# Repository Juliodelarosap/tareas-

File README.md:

# tareas-
tareas de programacion mecatronicos 
c3-2022
Nombre: Julio de la Rosa 
Matricula: 2018-6732

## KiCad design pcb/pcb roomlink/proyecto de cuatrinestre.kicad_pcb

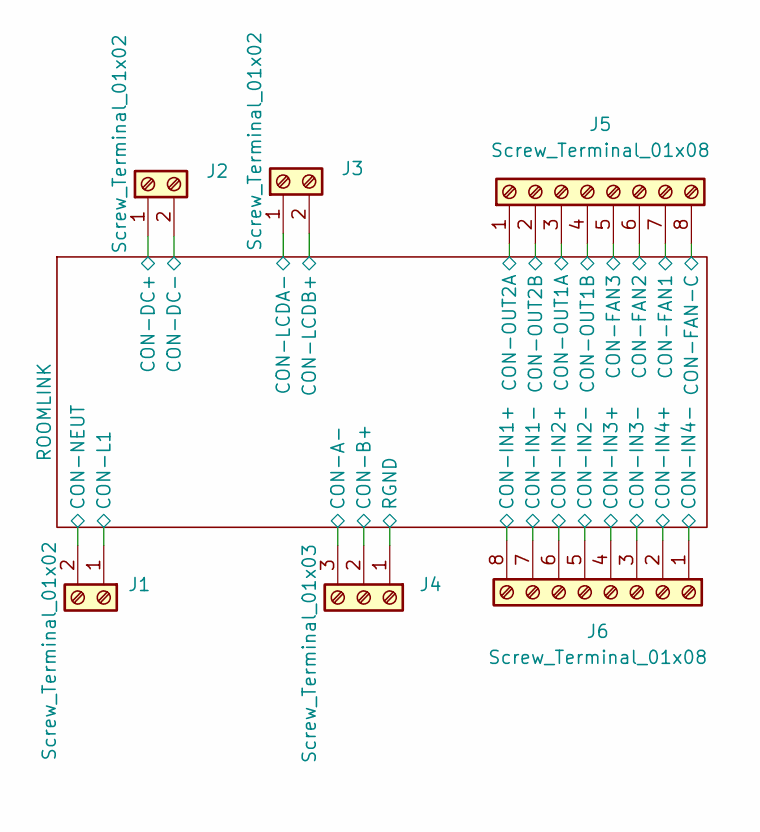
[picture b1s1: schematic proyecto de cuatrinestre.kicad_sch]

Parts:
J1, J2, J3: Screw_Terminal_01x02; CUI_TBP04R12-500-02GR
J4: Screw_Terminal_01x03; CUI_TBP04R12-500-03GR
J5, J6: Screw_Terminal_01x08; CUI_TBP04R12-500-08GR

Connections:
/ROOMLINK/CON-A-: J4.3; also elsewhere on the board
/ROOMLINK/CON-B+: J4.2; also elsewhere on the board
/ROOMLINK/CON-DC+: J2.1; also elsewhere on the board
/ROOMLINK/CON-DC-: J2.2; also elsewhere on the board
/ROOMLINK/CON-FAN1: J5.7; also elsewhere on the board
/ROOMLINK/CON-FAN2: J5.6; also elsewhere on the board
/ROOMLINK/CON-FAN3: J5.5; also elsewhere on the board
/ROOMLINK/CON-FAN-C: J5.8; also elsewhere on the board
/ROOMLINK/CON-IN1+: J6.8; also elsewhere on the board
/ROOMLINK/CON-IN1-: J6.7; also elsewhere on the board
/ROOMLINK/CON-IN2+: J6.6; also elsewhere on the board
/ROOMLINK/CON-IN2-: J6.5; also elsewhere on the board
/ROOMLINK/CON-IN3+: J6.4; also elsewhere on the board
/ROOMLINK/CON-IN3-: J6.3; also elsewhere on the board
/ROOMLINK/CON-IN4+: J6.2; also elsewhere on the board
/ROOMLINK/CON-IN4-: J6.1; also elsewhere on the board
/ROOMLINK/CON-L1: J1.1; also elsewhere on the board
/ROOMLINK/CON-LCDA-: J3.1; also elsewhere on the board
/ROOMLINK/CON-LCDB+: J3.2; also elsewhere on the board
/ROOMLINK/CON-NEUT: J1.2; also elsewhere on the board
/ROOMLINK/CON-OUT1A: J5.3; also elsewhere on the board
/ROOMLINK/CON-OUT1B: J5.4; also elsewhere on the board
/ROOMLINK/CON-OUT2A: J5.1; also elsewhere on the board
/ROOMLINK/CON-OUT2B: J5.2; also elsewhere on the board
/ROOMLINK/RGND: J4.1; also elsewhere on the board

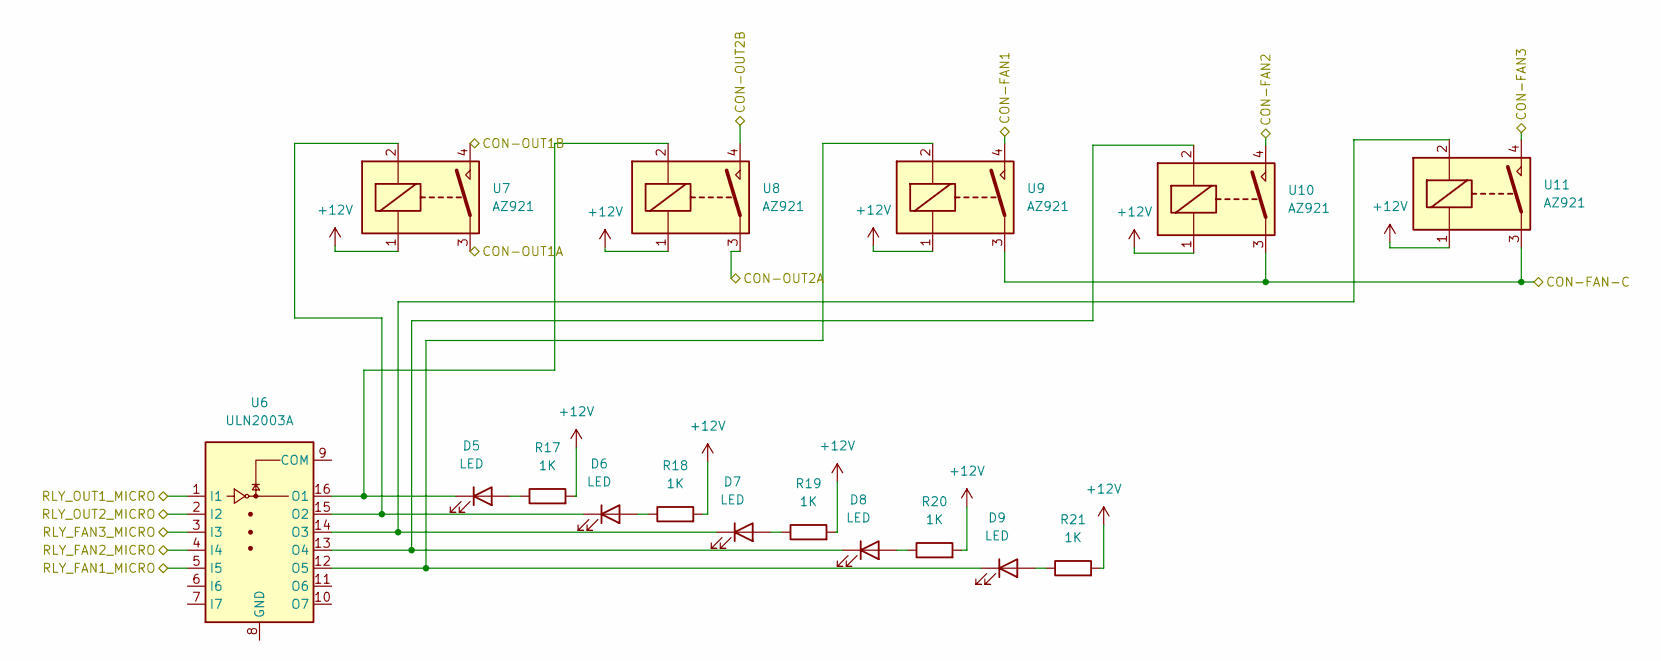
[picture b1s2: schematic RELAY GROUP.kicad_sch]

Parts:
D5, D6, D7, D8, D9: LED; LED_0805_2012Metric
R17, R18, R19, R20, R21: 1K; R_0805_2012Metric
U6: ULN2003A; SOIC-16_3.9x9.9mm_P1.27mm
U7, U8, U9, U10, U11: AZ921

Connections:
+12V: R17.2, R18.2, R19.2, R20.2, R21.2, U7.1, U8.1, U9.1, U10.1, U11.1; also elsewhere on the board
/ROOMLINK/CON-FAN1: U9.4; also elsewhere on the board
/ROOMLINK/CON-FAN2: U10.4; also elsewhere on the board
/ROOMLINK/CON-FAN3: U11.4; also elsewhere on the board
/ROOMLINK/CON-FAN-C: U9.3, U10.3, U11.3; also elsewhere on the board
/ROOMLINK/CON-OUT1A: U7.3; also elsewhere on the board
/ROOMLINK/CON-OUT1B: U7.4; also elsewhere on the board
/ROOMLINK/CON-OUT2A: U8.3; also elsewhere on the board
/ROOMLINK/CON-OUT2B: U8.4; also elsewhere on the board
/ROOMLINK/CONTROL/RLY_FAN1_MICRO: U6.5 (I5); also elsewhere on the board
/ROOMLINK/CONTROL/RLY_FAN2_MICRO: U6.4 (I4); also elsewhere on the board
/ROOMLINK/CONTROL/RLY_FAN3_MICRO: U6.3 (I3); also elsewhere on the board
/ROOMLINK/CONTROL/RLY_OUT1_MICRO: U6.1 (I1); also elsewhere on the board
/ROOMLINK/CONTROL/RLY_OUT2_MICRO: U6.2 (I2); also elsewhere on the board
unnamed: D5.2 (A), R17.1
unnamed: D5.1 (K), U6.16 (O1), U8.2
unnamed: D6.2 (A), R18.1
unnamed: D6.1 (K), U6.15 (O2), U7.2
unnamed: D7.2 (A), R19.1
unnamed: D7.1 (K), U6.14 (O3), U11.2
unnamed: D8.2 (A), R20.1
unnamed: D8.1 (K), U6.13 (O4), U10.2
unnamed: D9.2 (A), R21.1
unnamed: D9.1 (K), U6.12 (O5), U9.2

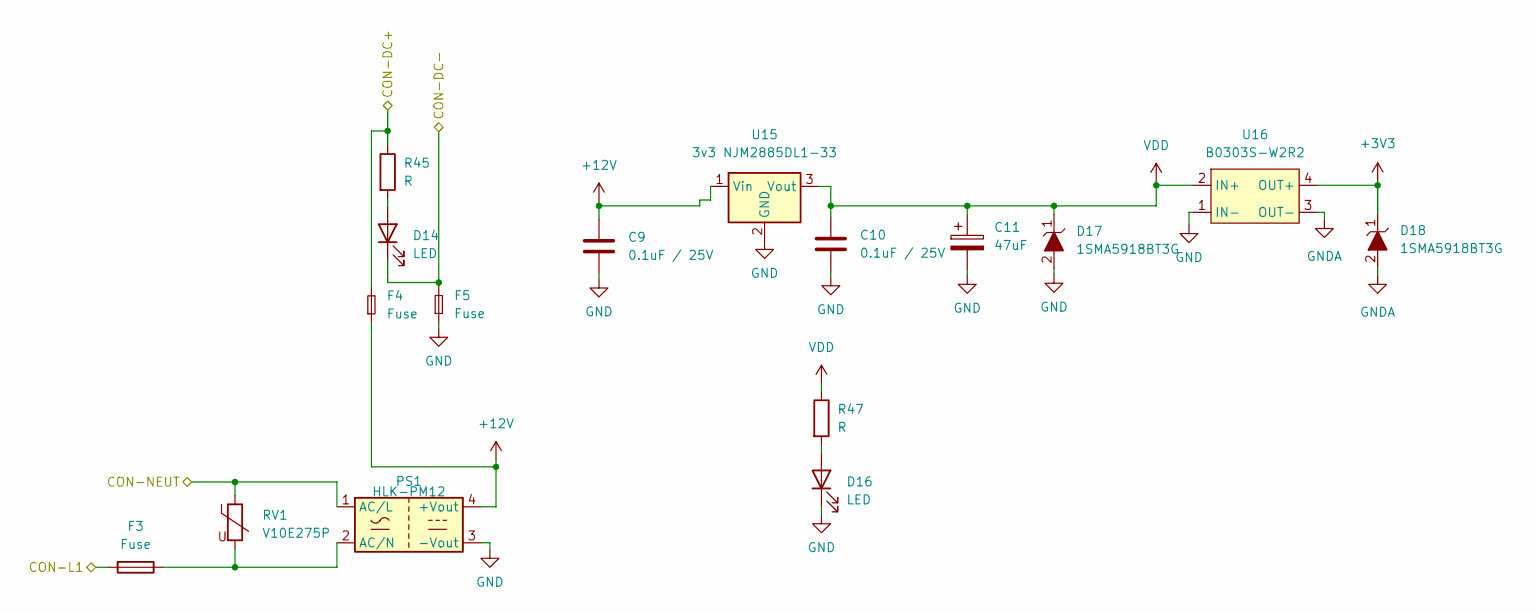
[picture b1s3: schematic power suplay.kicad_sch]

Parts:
C9, C10: 0.1uF / 25V; C_0805_2012Metric
C11: 47uF; CP_Elec_6.3x5.7
D14, D16: LED; LED_0805_2012Metric
D17, D18: 1SMA5918BT3G; D_SMB
F3: Fuse; Fuseholder_Cylinder-5x20mm_Schurter_0031_8201_Horizontal_Op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
F4, F5: Fuse; RESC3115X65N
PS1: HLK-PM12; Converter_ACDC_HiLink_HLK-PMxx
R45, R47: R; R_0805_2012Metric
RV1: V10E275P; VAR_B72210S1140K501
U15: 3v3 NJM2885DL1-33; TO-252-2
U16: B0303S-W2R2; CONV_B0505S-1WR2

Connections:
+3V3: D18.1, U16.4 (OUT+); also elsewhere on the board
+12V: C9.1, F4.1, PS1.4 (+Vout), U15.1 (Vin); also elsewhere on the board
/ROOMLINK/CON-DC+: F4.2, R45.1; also elsewhere on the board
/ROOMLINK/CON-DC-: D14.1 (K), F5.2; also elsewhere on the board
/ROOMLINK/CON-L1: F3.2; also elsewhere on the board
/ROOMLINK/CON-NEUT: PS1.1 (AC/L), RV1.1; also elsewhere on the board
GND: C9.2, C10.2, C11.2, D16.1 (K), D17.2, F5.1, PS1.3 (-Vout), U15.2 (GND), U16.1 (IN-); also elsewhere on the board
GNDA: D18.2, U16.3 (OUT-); also elsewhere on the board
unnamed: D14.2 (A), R45.2
unnamed: D16.2 (A), R47.2
unnamed: F3.1, PS1.2 (AC/N), RV1.2
VDD: C10.1, C11.1, D17.1, R47.1, U15.3 (Vout), U16.2 (IN+); also elsewhere on the board

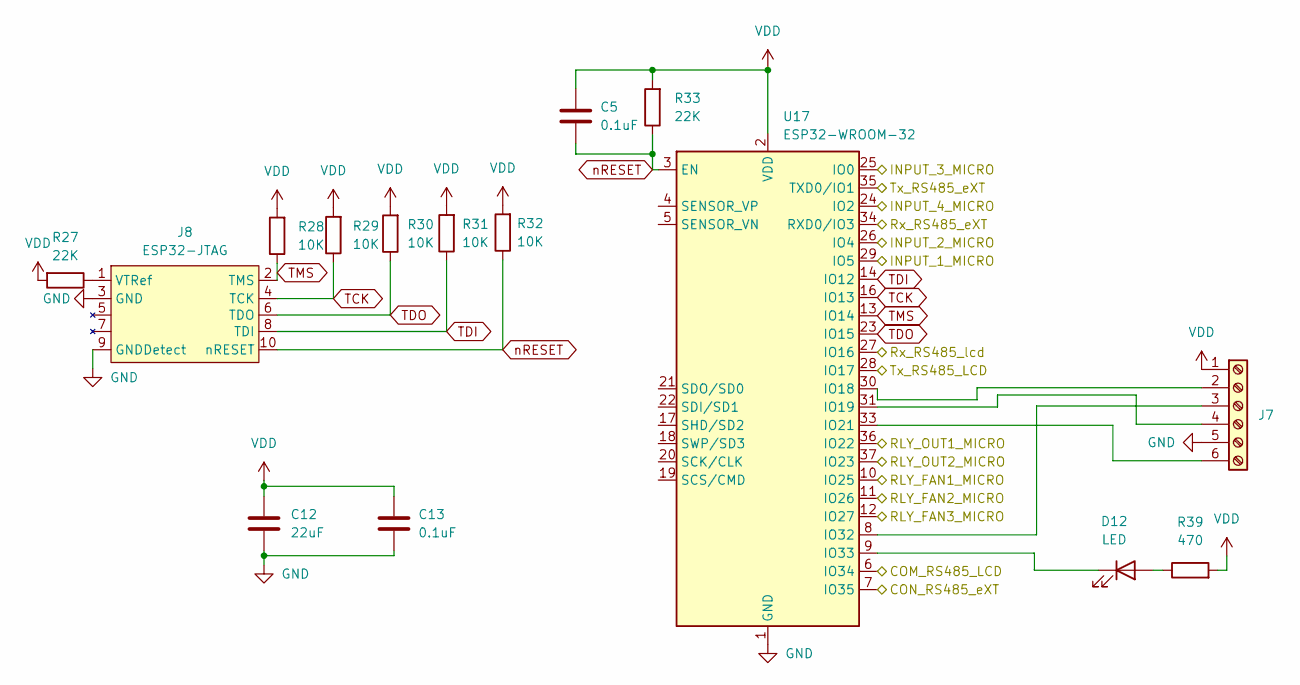
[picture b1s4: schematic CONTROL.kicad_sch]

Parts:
C5, C13: 0.1uF; C_0805_2012Metric
C12: 22uF; C_0805_2012Metric
D12: LED; LED_0805_2012Metric
J7: Screw_Terminal_01x06; PinHeader_2x03_P2.54mm_Vertical
J8: ESP32-JTAG; PinHeader_2x05_P2.54mm_Vertical
R27, R33: 22K; R_0805_2012Metric
R28, R29, R30, R31, R32: 10K; R_0805_2012Metric
R39: 470; R_0805_2012Metric
U17: ESP32-WROOM-32

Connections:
/ROOMLINK/CONTROL/COM_RS485_LCD: U17.6 (IO34); also elsewhere on the board
/ROOMLINK/CONTROL/CON_RS485_eXT: U17.7 (IO35); also elsewhere on the board
/ROOMLINK/CONTROL/INPUT_1_MICRO: U17.29 (IO5); also elsewhere on the board
/ROOMLINK/CONTROL/INPUT_2_MICRO: U17.26 (IO4); also elsewhere on the board
/ROOMLINK/CONTROL/INPUT_3_MICRO: U17.25 (IO0); also elsewhere on the board
/ROOMLINK/CONTROL/INPUT_4_MICRO: U17.24 (IO2); also elsewhere on the board
/ROOMLINK/CONTROL/RLY_FAN1_MICRO: U17.10 (IO25); also elsewhere on the board
/ROOMLINK/CONTROL/RLY_FAN2_MICRO: U17.11 (IO26); also elsewhere on the board
/ROOMLINK/CONTROL/RLY_FAN3_MICRO: U17.12 (IO27); also elsewhere on the board
/ROOMLINK/CONTROL/RLY_OUT1_MICRO: U17.36 (IO22); also elsewhere on the board
/ROOMLINK/CONTROL/RLY_OUT2_MICRO: U17.37 (IO23); also elsewhere on the board
/ROOMLINK/CONTROL/Rx_RS485_eXT: U17.34 (RXD0/IO3); also elsewhere on the board
/ROOMLINK/CONTROL/Rx_RS485_lcd: U17.27 (IO16); also elsewhere on the board
/ROOMLINK/CONTROL/Tx_RS485_LCD: U17.28 (IO17); also elsewhere on the board
/ROOMLINK/CONTROL/Tx_RS485_eXT: U17.35 (TXD0/IO1); also elsewhere on the board
GND: C12.2, C13.2, J7.5, J8.3 (GND), J8.9 (GNDDetect), U17.1 (GND), U17.15 (GND), U17.38 (GND), U17.39 (GND); also elsewhere on the board
unnamed: D12.2 (A), R39.1
unnamed: D12.1 (K), U17.9 (IO33)
unnamed: J7.2, U17.30 (IO18)
unnamed: J7.3, U17.8 (IO32)
unnamed: J7.4, U17.31 (IO19)
unnamed: J7.6, U17.33 (IO21)
unnamed: J8.1 (VTRef), R27.1
TCK: J8.4 (TCK), R29.1, U17.16 (IO13)
TDI: J8.8 (TDI), R31.1, U17.14 (IO12)
TDO: J8.6 (TDO), R30.1, U17.23 (IO15)
TMS: J8.2 (TMS), R28.1, U17.13 (IO14)
VDD: C5.1, C12.1, C13.1, J7.1, R27.2, R28.2, R29.2, R30.2, R31.2, R32.2, R33.2, R39.2, U17.2 (VDD); also elsewhere on the board
nRESET: C5.2, J8.10 (nRESET), R32.1, R33.1, U17.3 (EN)

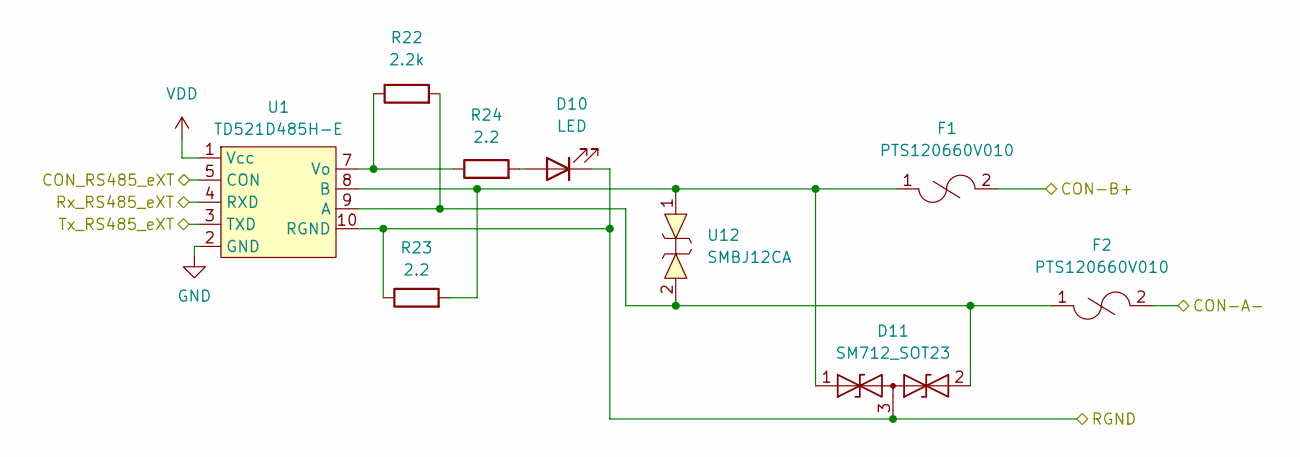
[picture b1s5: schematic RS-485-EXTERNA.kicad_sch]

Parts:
D10: LED; LED_0805_2012Metric
D11: SM712_SOT23; SOT-23
F1, F2: PTS120660V010; RESC3115X65N
R22: 2.2k; R_0805_2012Metric
R23, R24: 2.2; R_0805_2012Metric
U1: TD521D485H-E
U12: SMBJ12CA

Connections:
/ROOMLINK/CON-A-: F2.2; also elsewhere on the board
/ROOMLINK/CON-B+: F1.2; also elsewhere on the board
/ROOMLINK/CONTROL/CON_RS485_eXT: U1.5 (CON); also elsewhere on the board
/ROOMLINK/CONTROL/Rx_RS485_eXT: U1.4 (RXD); also elsewhere on the board
/ROOMLINK/CONTROL/Tx_RS485_eXT: U1.3 (TXD); also elsewhere on the board
/ROOMLINK/RGND: D10.1 (K), D11.3 (common), R23.1, U1.10 (RGND); also elsewhere on the board
GND: U1.2 (GND); also elsewhere on the board
unnamed: D10.2 (A), R24.2
unnamed: D11.1 (A1), F1.1, R23.2, U1.8 (B), U12.1
unnamed: D11.2 (A2), F2.1, R22.2, U1.9 (A), U12.2
unnamed: R22.1, R24.1, U1.7 (Vo)
VDD: U1.1 (Vcc); also elsewhere on the board

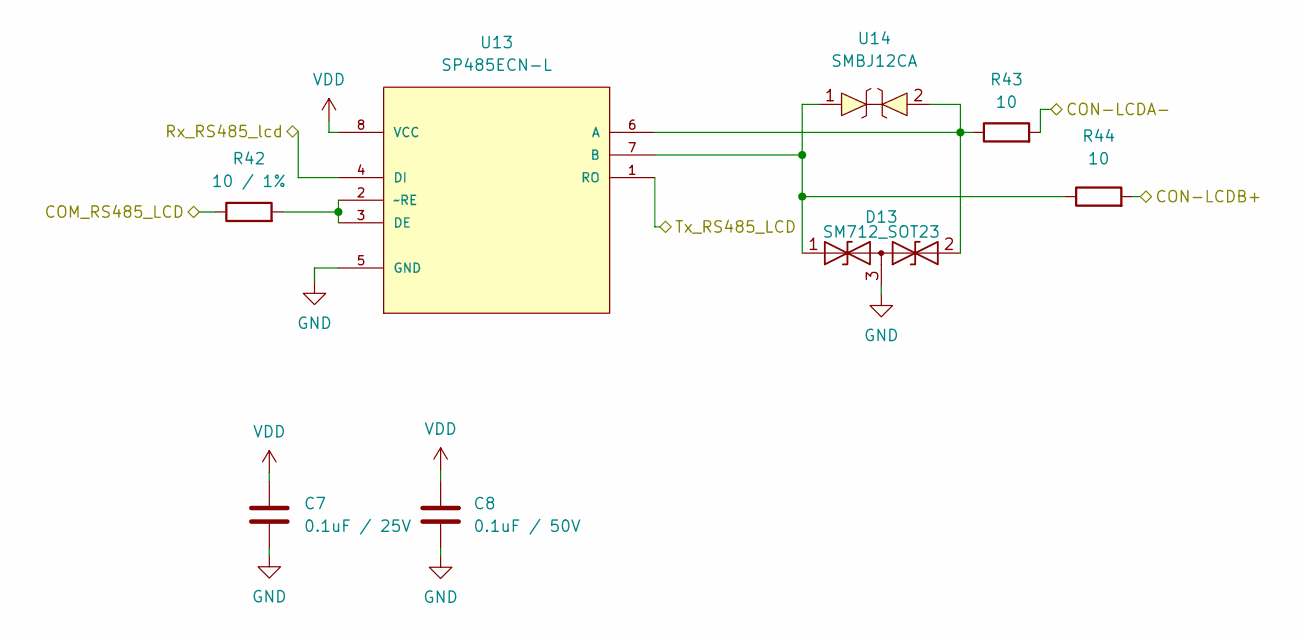
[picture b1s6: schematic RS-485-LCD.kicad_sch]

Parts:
C7: 0.1uF / 25V; C_0805_2012Metric
C8: 0.1uF / 50V; C_0805_2012Metric
D13: SM712_SOT23; SOT-23
R42: 10 / 1%; R_0805_2012Metric
R43, R44: 10; R_0805_2012Metric
U13: SP485ECN-L; SOIC127P600X175-8N; MPN SP485ECN-L
U14: SMBJ12CA

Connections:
/ROOMLINK/CON-LCDA-: R43.2; also elsewhere on the board
/ROOMLINK/CON-LCDB+: R44.2; also elsewhere on the board
/ROOMLINK/CONTROL/COM_RS485_LCD: R42.1; also elsewhere on the board
/ROOMLINK/CONTROL/Rx_RS485_lcd: U13.4 (DI); also elsewhere on the board
/ROOMLINK/CONTROL/Tx_RS485_LCD: U13.1 (RO); also elsewhere on the board
GND: C7.2, C8.2, D13.3 (common), U13.5 (GND); also elsewhere on the board
unnamed: D13.1 (A1), R44.1, U13.7 (B), U14.1
unnamed: D13.2 (A2), R43.1, U13.6 (A), U14.2
unnamed: R42.2, U13.2 (~RE), U13.3 (DE)
VDD: C7.1, C8.1, U13.8 (VCC); also elsewhere on the board

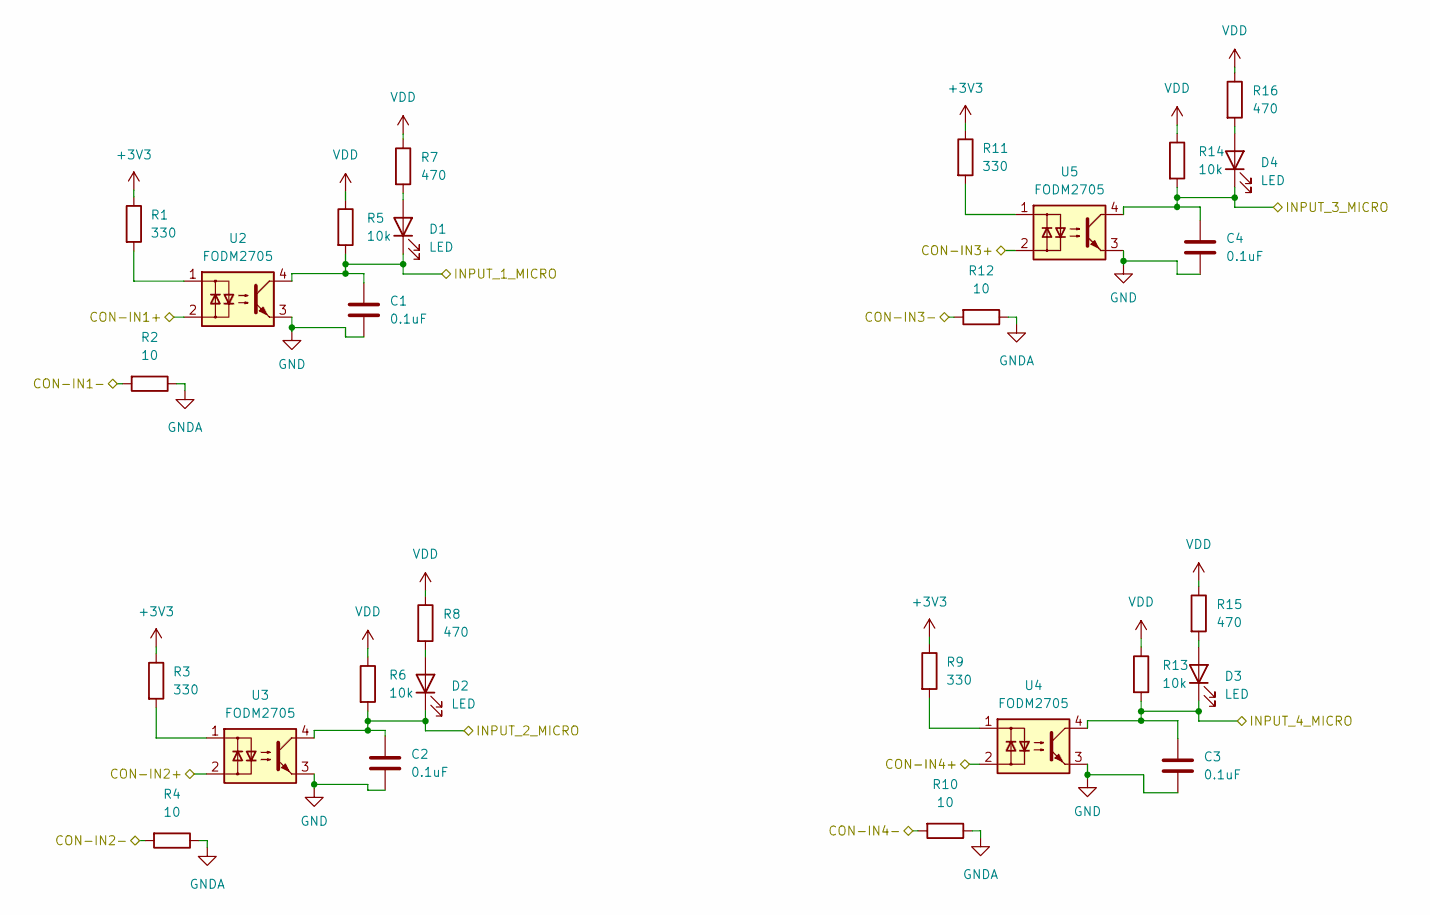
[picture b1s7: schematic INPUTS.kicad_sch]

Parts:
C1, C2, C3, C4: 0.1uF; C_0805_2012Metric
D1, D2, D3, D4: LED; LED_0805_2012Metric
R1, R3, R9, R11: 330; R_0805_2012Metric
R2, R4, R10, R12: 10; R_0805_2012Metric
R5, R6, R13, R14: 10k; R_0805_2012Metric
R7, R8, R15, R16: 470; R_0805_2012Metric
U2, U3, U4, U5: FODM2705

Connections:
+3V3: R1.1, R3.1, R9.1, R11.1; also elsewhere on the board
/ROOMLINK/CON-IN1+: U2.2; also elsewhere on the board
/ROOMLINK/CON-IN1-: R2.2; also elsewhere on the board
/ROOMLINK/CON-IN2+: U3.2; also elsewhere on the board
/ROOMLINK/CON-IN2-: R4.2; also elsewhere on the board
/ROOMLINK/CON-IN3+: U5.2; also elsewhere on the board
/ROOMLINK/CON-IN3-: R12.2; also elsewhere on the board
/ROOMLINK/CON-IN4+: U4.2; also elsewhere on the board
/ROOMLINK/CON-IN4-: R10.2; also elsewhere on the board
/ROOMLINK/CONTROL/INPUT_1_MICRO: C1.1, D1.1 (K), R5.2, U2.4; also elsewhere on the board
/ROOMLINK/CONTROL/INPUT_2_MICRO: C2.1, D2.1 (K), R6.2, U3.4; also elsewhere on the board
/ROOMLINK/CONTROL/INPUT_3_MICRO: C4.1, D4.1 (K), R14.2, U5.4; also elsewhere on the board
/ROOMLINK/CONTROL/INPUT_4_MICRO: C3.1, D3.1 (K), R13.2, U4.4; also elsewhere on the board
GND: C1.2, C2.2, C3.2, C4.2, U2.3, U3.3, U4.3, U5.3; also elsewhere on the board
GNDA: R2.1, R4.1, R10.1, R12.1; also elsewhere on the board
unnamed: D1.2 (A), R7.2
unnamed: D2.2 (A), R8.2
unnamed: D3.2 (A), R15.2
unnamed: D4.2 (A), R16.2
unnamed: R1.2, U2.1
unnamed: R3.2, U3.1
unnamed: R9.2, U4.1
unnamed: R11.2, U5.1
VDD: R5.1, R6.1, R7.1, R8.1, R13.1, R14.1, R15.1, R16.1; also elsewhere on the board

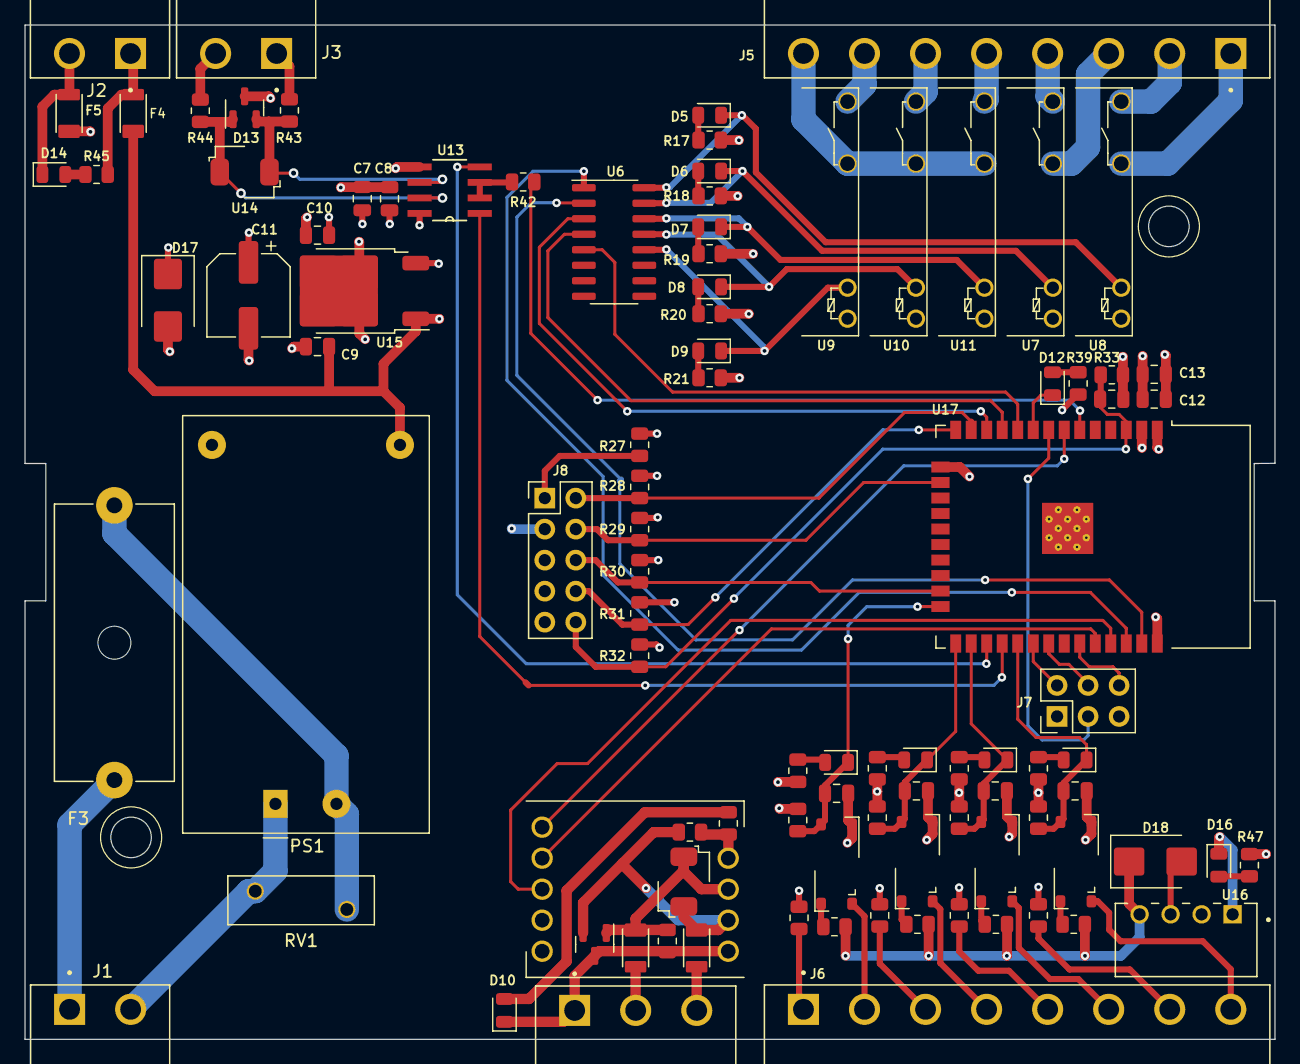
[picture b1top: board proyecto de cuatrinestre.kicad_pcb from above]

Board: 4 copper layers, 102.4 x 83.1 mm, 98 parts (0 on the bottom side), 85 nets.

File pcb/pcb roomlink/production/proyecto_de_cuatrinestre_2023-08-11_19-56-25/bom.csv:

Designator,Footprint,Quantity,Value,LCSC Part #
"C1, C13, C2, C3, C4, C5",0805,6,0.1uF,
"C10, C7, C9",0805,3,0.1uF / 25V,
C11,CP_Elec_6.3x5.7,1,47uF,
C12,0805,1,22uF,
C8,0805,1,0.1uF / 50V,
"D1, D10, D12, D14, D16, D2, D3, D4, D5, D6, D7, D8, D9",0805,13,LED,
"D11, D13",SOT-23,2,SM712_SOT23,
"D17, D18",D_SMB,2,1SMA5918BT3G,
"F1, F2",RESC3115X65N,2,PTS120660V010,
F3,Fuseholder_Cylinder-5x20mm_Schurter_0031_8201_Horizontal_Open,1,Fuse,
"F4, F5",RESC3115X65N,2,Fuse,
"J1, J2, J3",CUI_TBP04R12-500-02GR,3,Screw_Terminal_01x02,
J4,CUI_TBP04R12-500-03GR,1,Screw_Terminal_01x03,
"J5, J6",CUI_TBP04R12-500-08GR,2,Screw_Terminal_01x08,
J7,PinHeader_2x03_P2.54mm_Vertical,1,Screw_Terminal_01x06,
J8,PinHeader_2x05_P2.54mm_Vertical,1,ESP32-JTAG,
PS1,Converter_ACDC_HiLink_HLK-PMxx,1,HLK-PM12,
"R1, R11, R3, R9",0805,4,330,
"R10, R12, R2, R4, R43, R44",0805,6,10,
"R13, R14, R28, R29, R30, R31, R32, R5, R6",0805,9,10k,
"R15, R16, R39, R7, R8",0805,5,470,
"R17, R18, R19, R20, R21",0805,5,1K,
R22,0805,1,2.2k,
"R23, R24",0805,2,2.2,
"R27, R33",0805,2,22K,
R42,0805,1,10 / 1%,
"R45, R47",0805,2,R,
RV1,VAR_B72210S1140K501,1,V10E275P,
U1,TD521D485H-E,1,TD521D485H-E,
"U10, U11, U7, U8, U9",AZ921,5,AZ921,
"U12, U14",SMBJ12CA,2,SMBJ12CA,
U13,SOIC127P600X175-8N,1,SP485ECN-L,SP485ECN-L
U15,TO-252-2,1,3v3 NJM2885DL1-33,
U16,CONV_B0505S-1WR2,1,B0303S-W2R2,
U17,ESP32-WROOM-32,1,ESP32-WROOM-32,
"U2, U3, U4, U5",FODM2705,4,FODM2705,
U6,SOIC-16_3.9x9.9mm_P1.27mm,1,ULN2003A,

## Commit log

2022-10-31 funciones
2022-11-07 arreglos unidemiencionales
2022-11-14 cap 6
2022-11-14 cap7
2022-11-22 cap 7
2022-12-09 caps
2022-12-12 cap 8
2022-12-12 cap 9
